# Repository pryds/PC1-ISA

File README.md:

# Moved

The PC1-ISA project has been renamed to PC1-XT, and has moved to [GitLab](https://gitlab.com/autumnhippo/pc1-xt)

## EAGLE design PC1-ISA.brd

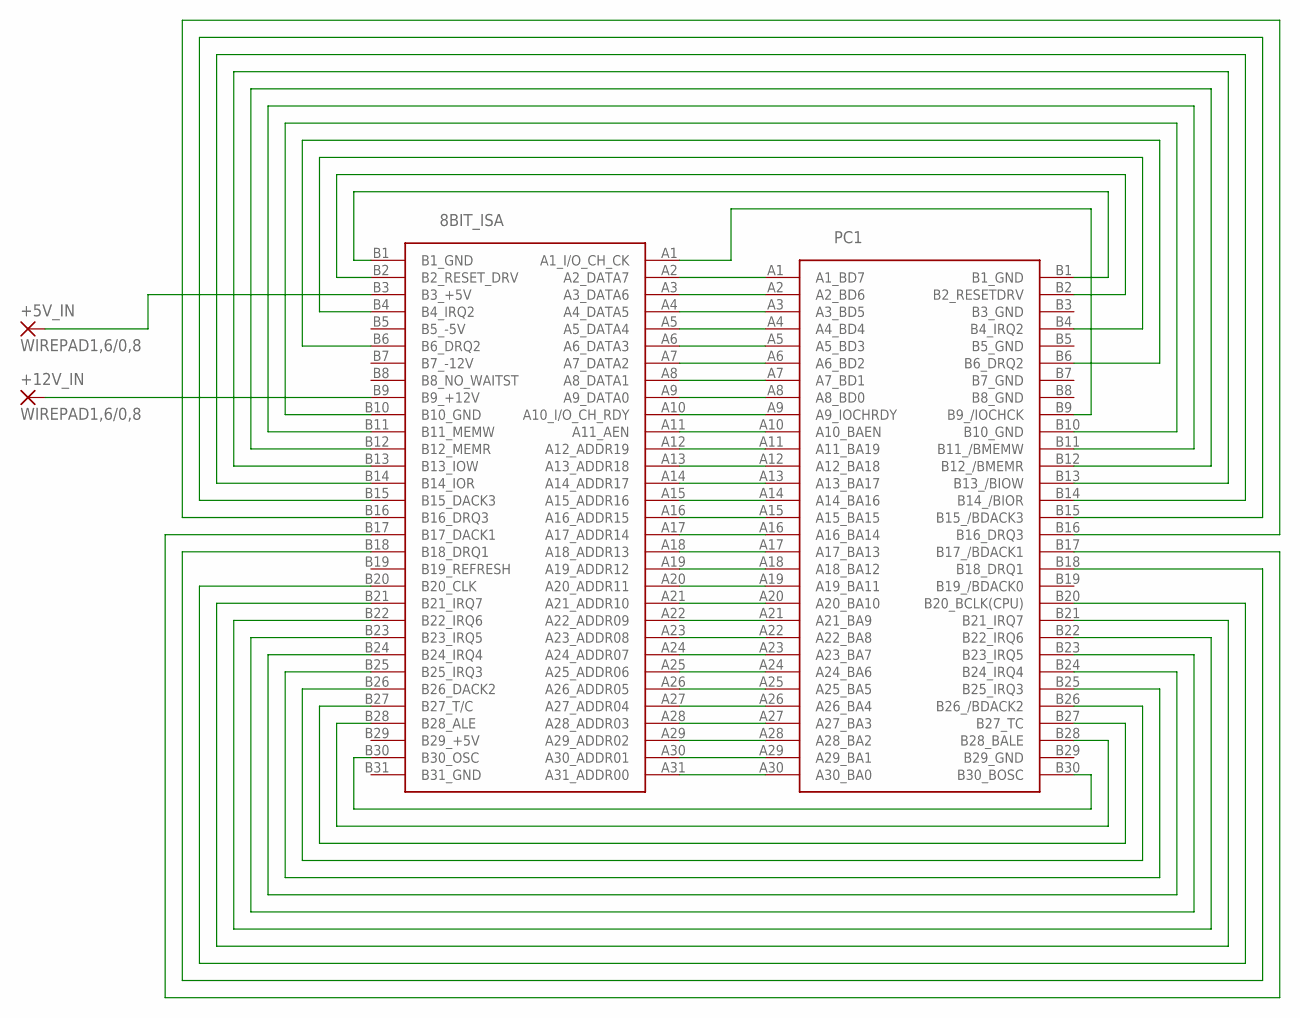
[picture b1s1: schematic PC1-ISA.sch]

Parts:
8BIT_ISA: CARDEDGE_FEMALE_62PINS_8BITISA_STRAIGHT
+5V_IN, +12V_IN: WIREPAD1,6/0,8; 1,6/0,8
PC1: CARDEDGE_FEMALE_60PINS_PC1_ANGLEDLEFT

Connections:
unnamed: 8BIT_ISA.A2 (A2_DATA7), PC1.A1 (A1_BD7)
unnamed: 8BIT_ISA.A3 (A3_DATA6), PC1.A2 (A2_BD6)
unnamed: 8BIT_ISA.A4 (A4_DATA5), PC1.A3 (A3_BD5)
unnamed: 8BIT_ISA.A5 (A5_DATA4), PC1.A4 (A4_BD4)
unnamed: 8BIT_ISA.A6 (A6_DATA3), PC1.A5 (A5_BD3)
unnamed: 8BIT_ISA.A7 (A7_DATA2), PC1.A6 (A6_BD2)
unnamed: 8BIT_ISA.A8 (A8_DATA1), PC1.A7 (A7_BD1)
unnamed: 8BIT_ISA.A9 (A9_DATA0), PC1.A8 (A8_BD0)
unnamed: 8BIT_ISA.A10 (A10_I/O_CH_RDY), PC1.A9 (A9_IOCHRDY)
unnamed: 8BIT_ISA.A11 (A11_AEN), PC1.A10 (A10_BAEN)
unnamed: 8BIT_ISA.A12 (A12_ADDR19), PC1.A11 (A11_BA19)
unnamed: 8BIT_ISA.A13 (A13_ADDR18), PC1.A12 (A12_BA18)
unnamed: 8BIT_ISA.A14 (A14_ADDR17), PC1.A13 (A13_BA17)
unnamed: 8BIT_ISA.A15 (A15_ADDR16), PC1.A14 (A14_BA16)
unnamed: 8BIT_ISA.A16 (A16_ADDR15), PC1.A15 (A15_BA15)
unnamed: 8BIT_ISA.A17 (A17_ADDR14), PC1.A16 (A16_BA14)
unnamed: 8BIT_ISA.A18 (A18_ADDR13), PC1.A17 (A17_BA13)
unnamed: 8BIT_ISA.A19 (A19_ADDR12), PC1.A18 (A18_BA12)
unnamed: 8BIT_ISA.A20 (A20_ADDR11), PC1.A19 (A19_BA11)
unnamed: 8BIT_ISA.A21 (A21_ADDR10), PC1.A20 (A20_BA10)
unnamed: 8BIT_ISA.A22 (A22_ADDR09), PC1.A21 (A21_BA9)
unnamed: 8BIT_ISA.A23 (A23_ADDR08), PC1.A22 (A22_BA8)
unnamed: 8BIT_ISA.A24 (A24_ADDR07), PC1.A23 (A23_BA7)
unnamed: 8BIT_ISA.A25 (A25_ADDR06), PC1.A24 (A24_BA6)
unnamed: 8BIT_ISA.A26 (A26_ADDR05), PC1.A25 (A25_BA5)
unnamed: 8BIT_ISA.A27 (A27_ADDR04), PC1.A26 (A26_BA4)
unnamed: 8BIT_ISA.A28 (A28_ADDR03), PC1.A27 (A27_BA3)
unnamed: 8BIT_ISA.A29 (A29_ADDR02), PC1.A28 (A28_BA2)
unnamed: 8BIT_ISA.A30 (A30_ADDR01), PC1.A29 (A29_BA1)
unnamed: 8BIT_ISA.A31 (A31_ADDR00), PC1.A30 (A30_BA0)
unnamed: 8BIT_ISA.A1 (A1_I/O_CH_CK), PC1.B9 (B9_/IOCHCK)
unnamed: 8BIT_ISA.B1 (B1_GND), PC1.B1 (B1_GND)
unnamed: 8BIT_ISA.B2 (B2_RESET_DRV), PC1.B2 (B2_RESETDRV)
unnamed: 8BIT_ISA.B4 (B4_IRQ2), PC1.B4 (B4_IRQ2)
unnamed: 8BIT_ISA.B6 (B6_DRQ2), PC1.B6 (B6_DRQ2)
unnamed: 8BIT_ISA.B10 (B10_GND), PC1.B10 (B10_GND)
unnamed: 8BIT_ISA.B11 (B11_MEMW), PC1.B11 (B11_/BMEMW)
unnamed: 8BIT_ISA.B12 (B12_MEMR), PC1.B12 (B12_/BMEMR)
unnamed: 8BIT_ISA.B30 (B30_OSC), PC1.B30 (B30_BOSC)
unnamed: 8BIT_ISA.B28 (B28_ALE), PC1.B28 (B28_BALE)
unnamed: 8BIT_ISA.B27 (B27_T/C), PC1.B27 (B27_TC)
unnamed: 8BIT_ISA.B26 (B26_DACK2), PC1.B26 (B26_/BDACK2)
unnamed: 8BIT_ISA.B25 (B25_IRQ3), PC1.B25 (B25_IRQ3)
unnamed: 8BIT_ISA.B24 (B24_IRQ4), PC1.B24 (B24_IRQ4)
unnamed: 8BIT_ISA.B23 (B23_IRQ5), PC1.B23 (B23_IRQ5)
unnamed: 8BIT_ISA.B22 (B22_IRQ6), PC1.B22 (B22_IRQ6)
unnamed: 8BIT_ISA.B21 (B21_IRQ7), PC1.B21 (B21_IRQ7)
unnamed: 8BIT_ISA.B13 (B13_IOW), PC1.B13 (B13_/BIOW)
unnamed: 8BIT_ISA.B14 (B14_IOR), PC1.B14 (B14_/BIOR)
unnamed: 8BIT_ISA.B15 (B15_DACK3), PC1.B15 (B15_/BDACK3)
unnamed: 8BIT_ISA.B16 (B16_DRQ3), PC1.B16 (B16_DRQ3)
unnamed: 8BIT_ISA.B20 (B20_CLK), PC1.B20 (B20_BCLK(CPU))
unnamed: 8BIT_ISA.B18 (B18_DRQ1), PC1.B18 (B18_DRQ1)
unnamed: 8BIT_ISA.B17 (B17_DACK1), PC1.B17 (B17_/BDACK1)
unnamed: 8BIT_ISA.B3 (B3_+5V), +5V_IN.1
unnamed: 8BIT_ISA.B9 (B9_+12V), +12V_IN.1

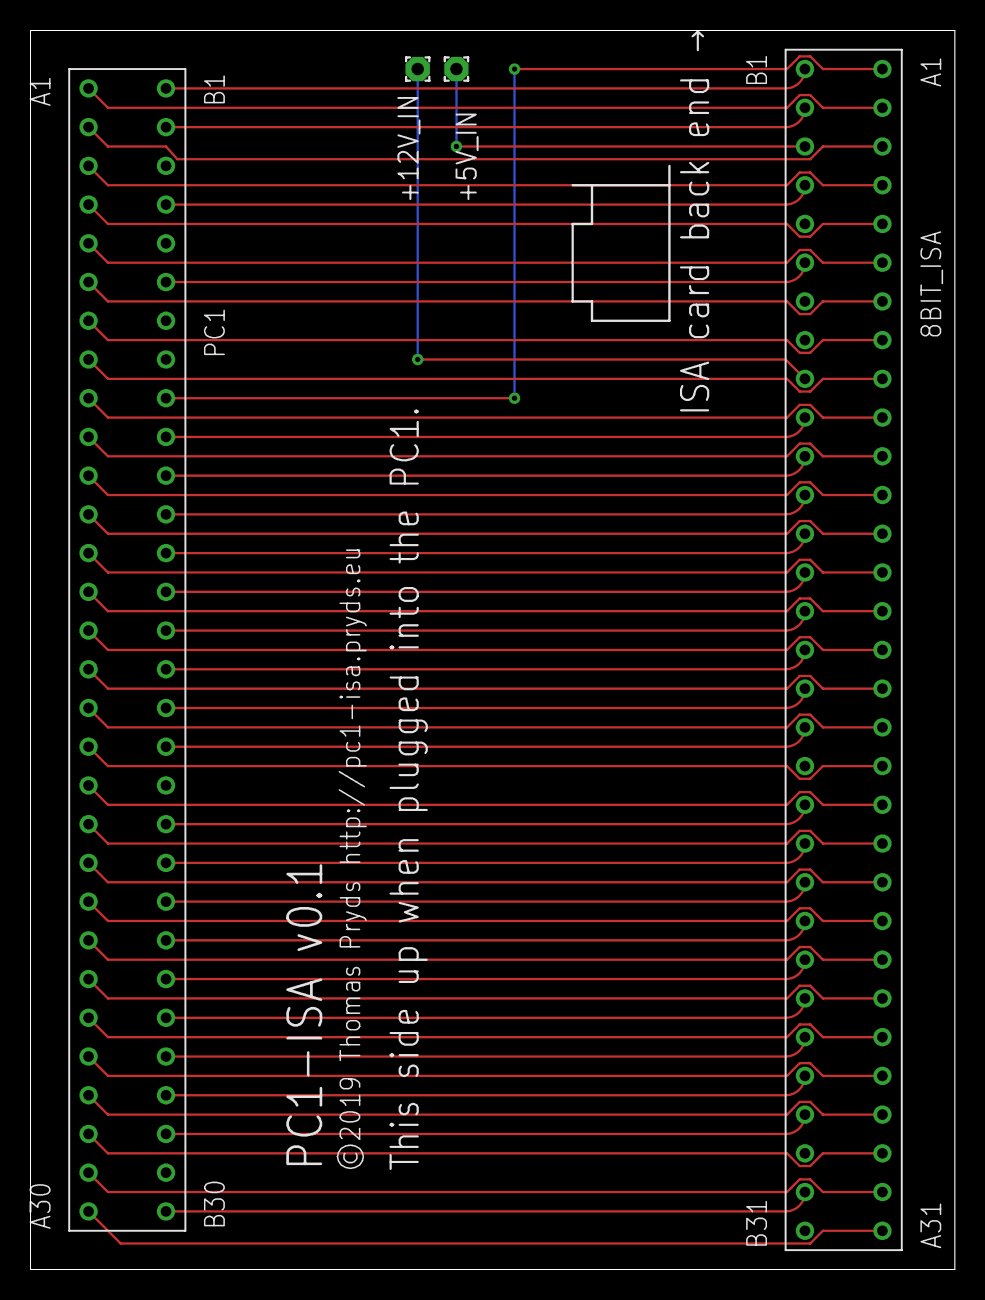
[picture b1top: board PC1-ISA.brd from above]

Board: 2 copper layers, 60.6 x 81.3 mm, 4 parts (0 on the bottom side), 56 nets.

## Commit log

2019-02-05 v0.1 files
2021-08-05 Project moved to GitLab

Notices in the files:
PC1-ISA.brd:
©2019 Thomas Pryds http://pc1-isa.pryds.eu
